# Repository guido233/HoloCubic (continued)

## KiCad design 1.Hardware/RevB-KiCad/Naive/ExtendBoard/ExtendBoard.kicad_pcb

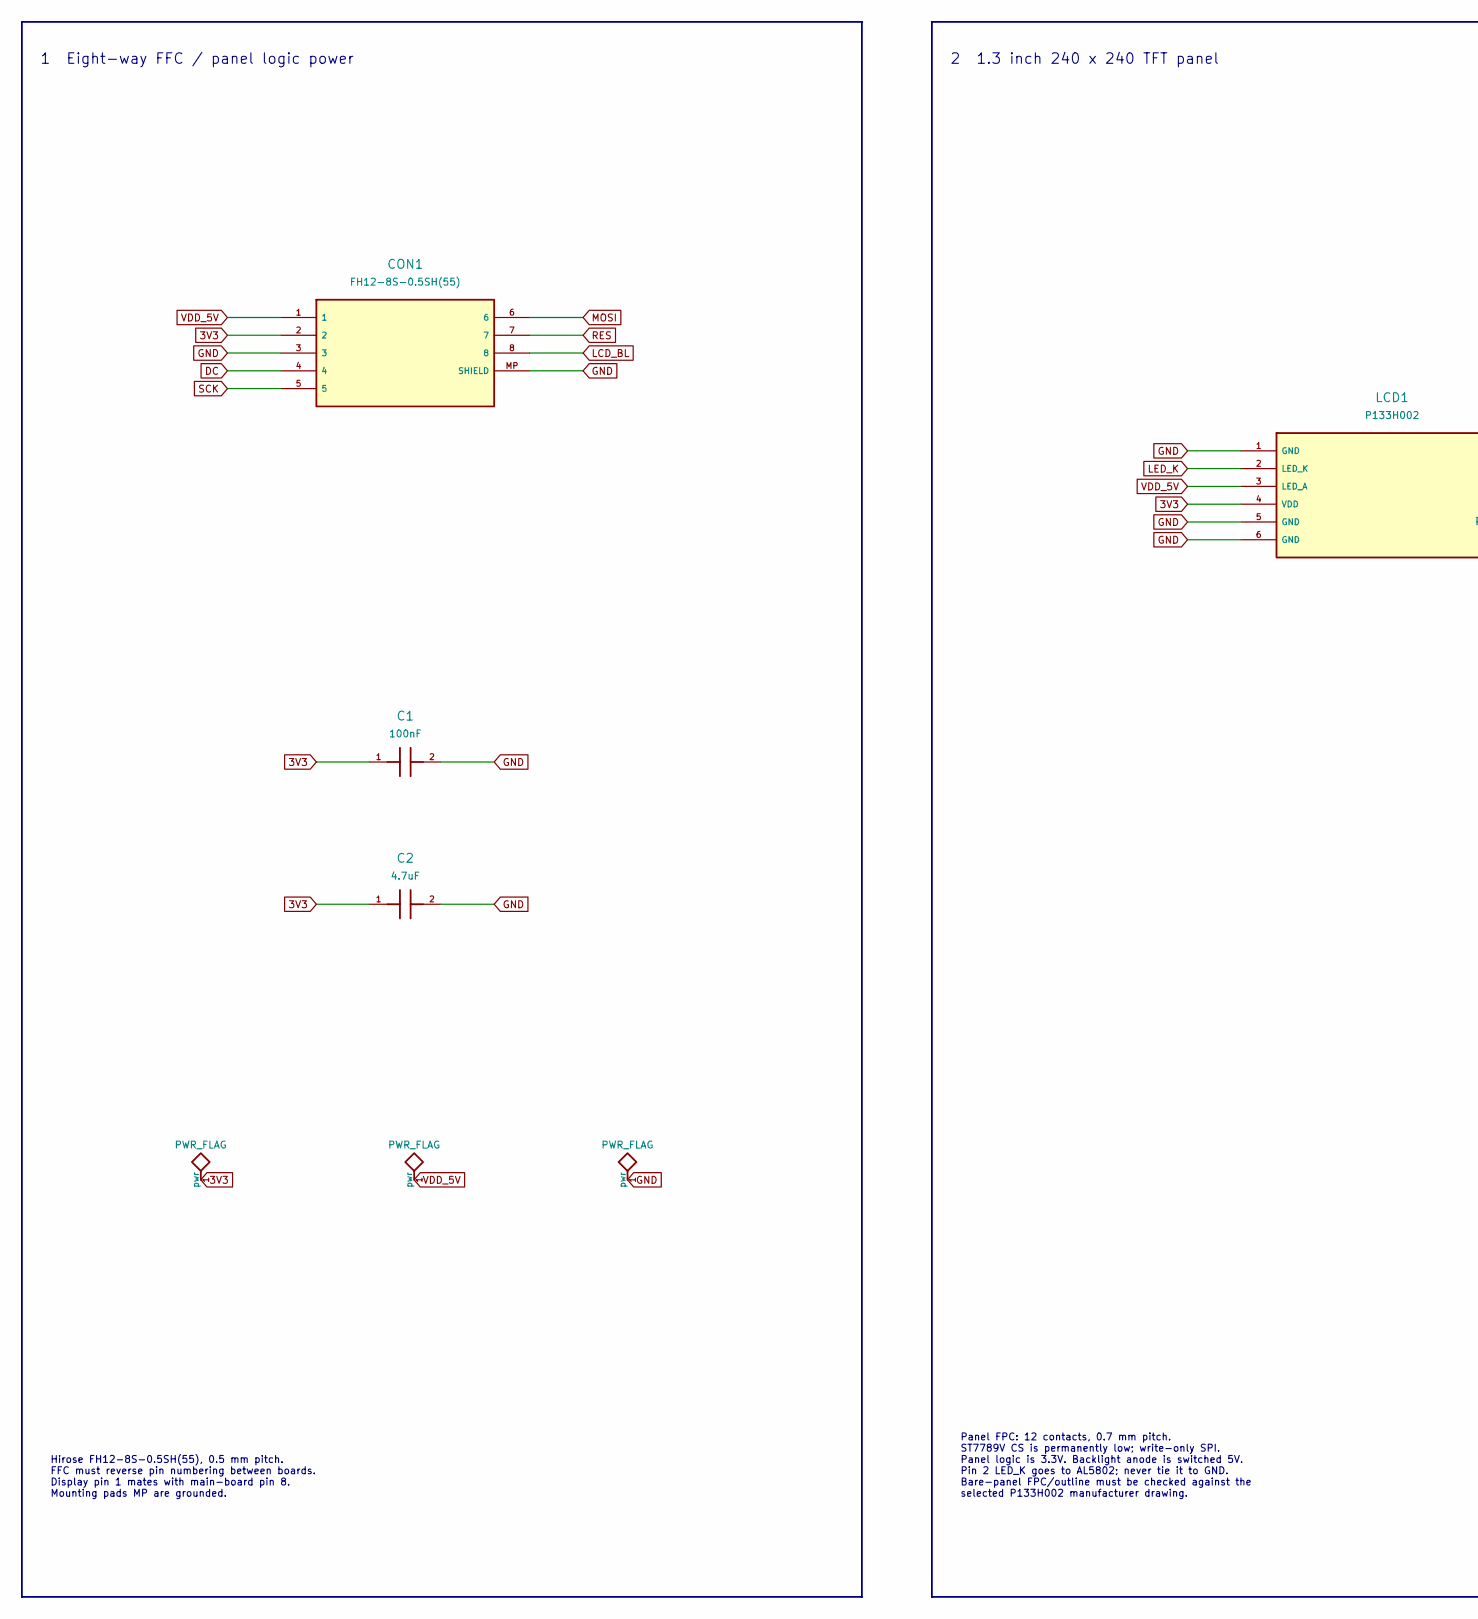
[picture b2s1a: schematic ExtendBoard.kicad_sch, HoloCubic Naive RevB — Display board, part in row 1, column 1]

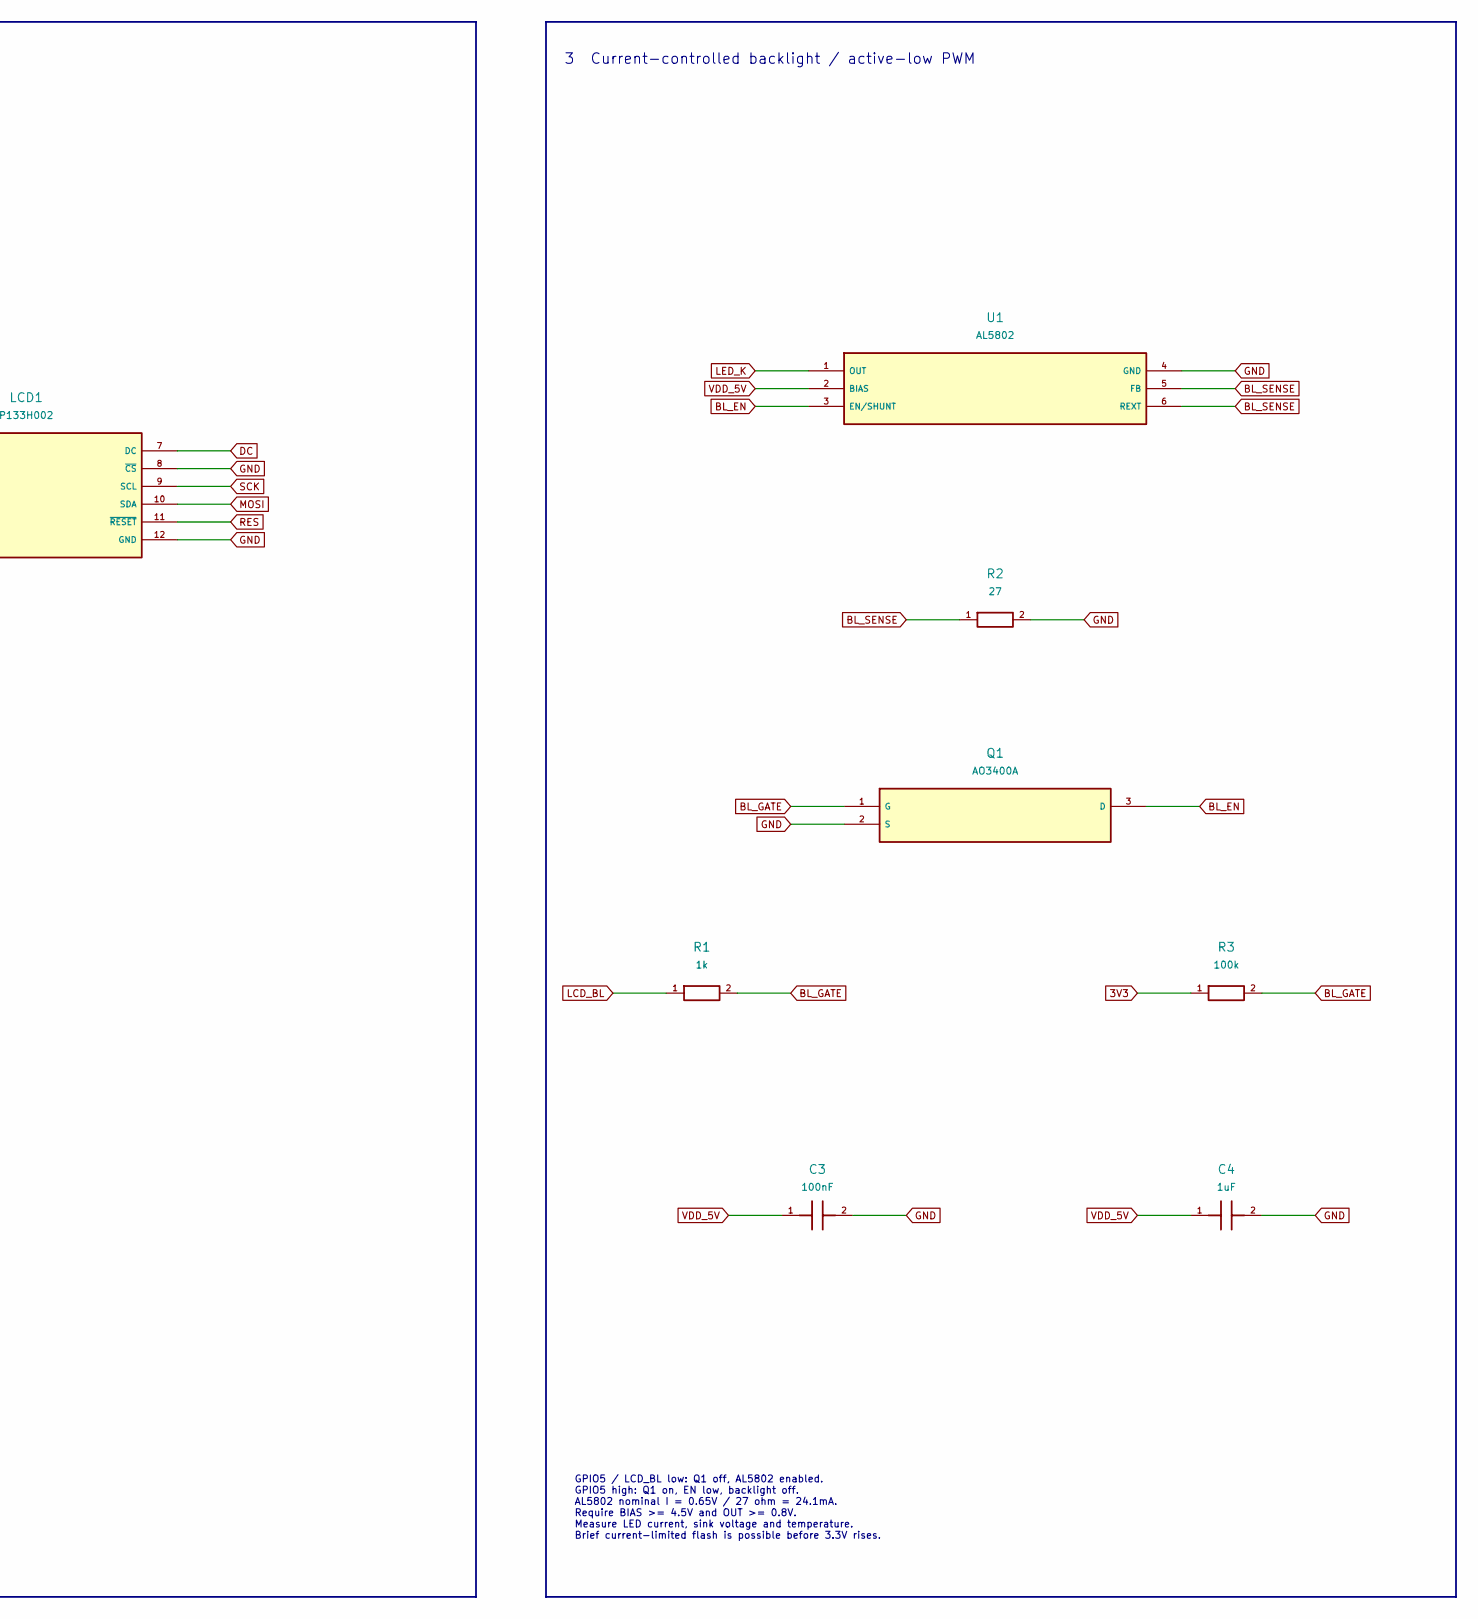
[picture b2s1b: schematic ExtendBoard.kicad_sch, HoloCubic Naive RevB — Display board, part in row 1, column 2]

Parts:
C1, C3: 100nF; C_0402; MPN GRM155R71C104KA88D
C2: 4.7uF; C_0603; MPN GRM188R61A475KE15D
C4: 1uF; C_0603; MPN GRM188R71E105KA12D
CON1: FH12-8S-0.5SH(55); FFC_8P_0.5mm; MPN FH12-8S-0.5SH(55)
LCD1: P133H002; LCD_12P_0.7mm; MPN P133H002
Q1: AO3400A; SOT23_NMOS; MPN AO3400A
R1: 1k; R_0402; MPN RC0402FR-071KL
R2: 27; R_0603; MPN RC0603FR-0727RL
R3: 100k; R_0402; MPN RC0402FR-07100KL
U1: AL5802; SOT26_AL5802; MPN AL5802-7

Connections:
3V3: C1.1, C2.1, CON1.2, LCD1.4 (VDD), R3.1
BL_EN: Q1.3 (D), U1.3 (EN/SHUNT)
BL_GATE: Q1.1 (G), R1.2, R3.2
BL_SENSE: R2.1, U1.5 (FB), U1.6 (REXT)
DC: CON1.4, LCD1.7 (DC)
GND: C1.2, C2.2, C3.2, C4.2, CON1.3, CON1.MP (SHIELD), LCD1.1 (GND), LCD1.5 (GND), LCD1.6 (GND), LCD1.8 (~CS), LCD1.12 (GND), Q1.2 (S), R2.2, U1.4 (GND)
LCD_BL: CON1.8, R1.1
LED_K: LCD1.2 (LED_K), U1.1 (OUT)
MOSI: CON1.6, LCD1.10 (SDA)
RES: CON1.7, LCD1.11 (~RESET)
SCK: CON1.5, LCD1.9 (SCL)
VDD_5V: C3.1, C4.1, CON1.1, LCD1.3 (LED_A), U1.2 (BIAS)

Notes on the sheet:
1 Eight-way FFC / panel logic power
2 1.3 inch 240 x 240 TFT panel
3 Current-controlled backlight / active-low PWM
Hirose FH12-8S-0.5SH(55), 0.5 mm pitch. FFC must reverse pin numbering between boards. Display pin 1 mates with main-board pin 8. Mounting pads MP are grounded.
Panel FPC: 12 contacts, 0.7 mm pitch. ST7789V CS is permanently low; write-only SPI. Panel logic is 3.3V. Backlight anode is switched 5V. Pin 2 LED_K goes to AL5802; never tie it to GND. Bare-panel FPC/outline must be checked against the selected P133H002 manufacturer drawing.
GPIO5 / LCD_BL low: Q1 off, AL5802 enabled. GPIO5 high: Q1 on, EN low, backlight off. AL5802 nominal I = 0.65V / 27 ohm = 24.1mA. Require BIAS >= 4.5V and OUT >= 0.8V. Measure LED current, sink voltage and temperature. Brief current-limited flash is possible before 3.3V rises.

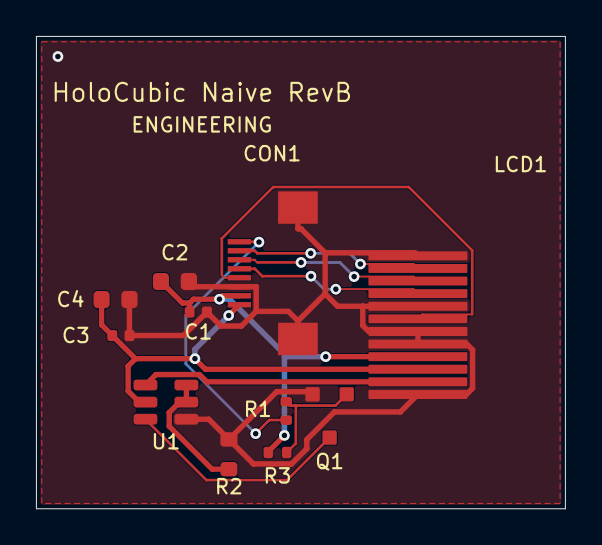
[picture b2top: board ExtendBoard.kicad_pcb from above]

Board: 2 copper layers, 29.4 x 26.2 mm, 11 parts (1 on the bottom side), 12 nets.

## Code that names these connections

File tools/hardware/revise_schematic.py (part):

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        'footprint': 'TF-Card-Amphenol with TF',
        'uuid': '036f4eda-700d-41ff-ba17-68fad1ad7e32',
        'pins': {'1': {'name': 'DATA_LINE[BIT_2]', 'type': 'passive', 'net': None},
                 '2': {'name': 'CARD_DETECT/DATA_LINE[BIT_3]', 'type': 'passive', 'net': 'GPIO15'},
                 '3': {'name': 'COMMAND/RESPONSE', 'type': 'passive', 'net': 'GPIO13'},
                 '4': {'name': 'VCC', 'type': 'passive', 'net': '3V3'},
                 '5': {'name': 'CLOCK', 'type': 'passive', 'net': 'GPIO14'},
                 '6': {'name': 'GND', 'type': 'passive', 'net': 'GND'},
                 '7': {'name': 'DATA_LINE[BIT_0]', 'type': 'passive', 'net': 'GPIO26'},
                 '8': {'name': 'DATA_LINE[BIT_1]', 'type': 'passive', 'net': None},
                 '9': {'name': 'CD_SWITCH1', 'type': 'passive', 'net': 'GND'},
                 '10': {'name': 'CD_SWITCH2', 'type': 'passive', 'net': 'GND'},
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 'R4': {'value': '12K',
        'footprint': 'RES_0402',
        'uuid': '480a12a3-30de-4506-819f-f5caa71d6bf5',
        'pins': {'1': {'name': '1', 'type': 'passive', 'net': 'DTR'},
                 '2': {'name': '2', 'type': 'passive', 'net': 'NetR4_2'}}},
 'USB1': {'value': 'Type-C',
          'footprint': 'Type-C-TOP',
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        'pins': {'1': {'name': 'VDD', 'type': 'power_in', 'net': 'VDD_5V'},
                 '2': {'name': 'DOUT', 'type': 'output', 'net': None},
                 '3': {'name': 'GND', 'type': 'power_in', 'net': 'GND'},
                 '4': {'name': 'DIN', 'type': 'input', 'net': 'GPIO27'}}},
 'R8': {'value': '10K',
        'footprint': 'RES_0402',
        'uuid': '4bc8dee3-f30c-4e77-bfd4-e8b4b71b5e3c',
        'pins': {'1': {'name': '1', 'type': 'passive', 'net': '3V3'},
                 '2': {'name': '2', 'type': 'passive', 'net': 'GPIO13'}}},
 'C2': {'value': '10uF',
        'footprint': 'CAP_0402',
        'uuid': '4edd19f1-0a79-4163-81b8-24c11d2702e3',
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        'footprint': 'RES_0402',
        'uuid': '59df2c9e-d16b-432e-aa8c-63f372a108e6',
        'pins': {'1': {'name': '1', 'type': 'passive', 'net': '3V3'},
                 '2': {'name': '2', 'type': 'passive', 'net': 'GPIO14'}}},
 'R7': {'value': '10K',
        'footprint': 'RES_0402',
        'uuid': '5a997410-384c-4189-9b8c-871480810be4',
        'pins': {'1': {'name': '1', 'type': 'passive', 'net': '3V3'},
                 '2': {'name': '2', 'type': 'passive', 'net': 'GPIO26'}}},
 'U1': {'value': 'CP2102',
        'footprint': 'QFN-28',
        'uuid': '6d990930-ca24-4125-89d4-8b4e6e54561f',
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 'R5': {'value': '12K',
        'footprint': 'RES_0402',
        'uuid': '7286ff2e-9e1b-4bae-ac24-8b4b0fb69403',
        'pins': {'1': {'name': '1', 'type': 'passive', 'net': 'RTS'},
                 '2': {'name': '2', 'type': 'passive', 'net': 'NetR5_2'}}},
 'U2': {'value': 'LP2992 3V3',
        'footprint': 'SOT23-5',
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 'R3': {'value': '200R',
        'footprint': 'RES_0402',
        'uuid': '7b4fecf7-ec40-466a-be5f-b7976867abfa',
        'pins': {'1': {'name': '1', 'type': 'passive', 'net': 'CP_Tx'},
                 '2': {'name': '2', 'type': 'passive', 'net': 'NetR3_2'}}},
 'R2': {'value': '0R',
        'footprint': 'RES_0402',
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         'uuid': '83ae2094-2acd-4f46-aec4-3455790201f2',
         'pins': {'1': {'name': 'B', 'type': 'input', 'net': 'NetR5_2'},
                  '2': {'name': 'E', 'type': 'passive', 'net': 'DTR'},
                  '3': {'name': 'C', 'type': 'open_collector', 'net': 'GPIO0'}}},
 'R6': {'value': '10K',
        'footprint': 'RES_0402',
        'uuid': '89beacb9-08aa-4d86-9ed8-5e2130c5a1e4',
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         'footprint': 'RES_0402',
         'uuid': '9a86d532-7819-4493-8d96-e85e307444ba',
         'pins': {'1': {'name': '1', 'type': 'passive', 'net': '3V3'},
                  '2': {'name': '2', 'type': 'passive', 'net': 'GPIO15'}}},
 'C10': {'value': '0.1uF',
         'footprint': 'CAP_0402',
         'uuid': '9b7b0381-cbbd-4e1e-85f8-db3f8b7ed2db',
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 'CON1': {'value': 'FFC_0.5_8',
          'footprint': 'FFC_0.5_8',
          'uuid': 'b2720441-1512-49fe-ba01-9b313defc353',
          'pins': {'1': {'name': '1', 'type': 'passive', 'net': 'GPIO5'},
                   '2': {'name': '2', 'type': 'passive', 'net': 'GPIO4'},
                   '3': {'name': '3', 'type': 'passive', 'net': 'GPIO23'},
                   '4': {'name': '4', 'type': 'passive', 'net': 'GPIO18'},
                   '5': {'name': '5', 'type': 'passive', 'net': 'DC'},
                   '6': {'name': '6', 'type': 'passive', 'net': 'GND'},
                   '7': {'name': '7', 'type': 'passive', 'net': '3V3'},
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                 '12': {'name': '32K_XP', 'type': 'bidirectional', 'net': 'BH_SDA'},
                 '13': {'name': '32K_XN', 'type': 'bidirectional', 'net': 'BH_SCL'},
                 '14': {'name': 'GPIO25', 'type': 'bidirectional', 'net': None},
                 '15': {'name': 'GPIO26', 'type': 'bidirectional', 'net': 'GPIO26'},
                 '16': {'name': 'GPIO27', 'type': 'bidirectional', 'net': 'GPIO27'},
                 '17': {'name': 'MTMS', 'type': 'bidirectional', 'net': 'GPIO14'},
                 '18': {'name': 'MTDI', 'type': 'bidirectional', 'net': None},
                 '19': {'name': 'VDD3P3_RTC', 'type': 'power_in', 'net': '3V3A'},
                 '20': {'name': 'MTCK', 'type': 'bidirectional', 'net': 'GPIO13'},
                 '21': {'name': 'MTDO', 'type': 'bidirectional', 'net': 'GPIO15'},
                 '22': {'name': 'GPIO2', 'type': 'bidirectional', 'net': 'DC'},
                 '23': {'name': 'GPIO0', 'type': 'bidirectional', 'net': 'GPIO0'},
                 '24': {'name': 'GPIO4', 'type': 'bidirectional', 'net': 'GPIO4'},
                 '25': {'name': 'IO16(FLASH_CS)', 'type': 'bidirectional', 'net': None},
                 '26': {'name': 'VDD_SDIO_NC', 'type': 'no_connect', 'net': None},
                 '27': {'name': 'IO17(FLASH_SD0)', 'type': 'bidirectional', 'net': None},
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                 '31': {'name': 'SD_CLK(FLASH_CLK)', 'type': 'bidirectional', 'net': None},
                 '32': {'name': 'SD_DATA_0(FLASH_SD3)', 'type': 'bidirectional', 'net': None},
                 '33': {'name': 'SD_DATA_1(FLASH_SD1)', 'type': 'bidirectional', 'net': None},
                 '34': {'name': 'GPIO5', 'type': 'bidirectional', 'net': 'GPIO5'},
                 '35': {'name': 'GPIO18', 'type': 'bidirectional', 'net': 'GPIO18'},
                 '36': {'name': 'GPIO23', 'type': 'bidirectional', 'net': 'GPIO23'},
                 '37': {'name': 'VDD3P3_CPU', 'type': 'power_in', 'net': '3V3A'},
                 '38': {'name': 'GPIO19', 'type': 'bidirectional', 'net': None},
                 '39': {'name': 'GPIO22', 'type': 'bidirectional', 'net': None},
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        doc += [rect,text_node(title,x1+2.54,y1+6.35,1.5)]
    notes=[('USB_VBUS = connector raw 5V; VDD_5V = switched system 5V.\nCC1 / CC2 each have an independent 5.1k Rd.',14,155),
           ('ON RC: 100k / 100nF; CT: 100pF C0G. 5V tR approx 0.425ms.\nMeasure CP_VDD rise to 2.7V <=1ms and USB hot-plug current.',214,164),
           ('OE permanently enabled; GPIO27 pulled low at reset.\nD1: Worldsemi WS2812B-V5/W. Series 33 ohm near buffer.',419,152),
           ('CP2102 internal 3.3V is CP_VDD, with C18 local bypass.\nR6 / C7 provide the ESP32 EN reset delay.\nDual NPN DTR/RTS topology retained from the original design.',14,369),
           ('Unused exposed flash / strapping / ADC pins are explicitly NC.\nGPIO32 = SDA; GPIO33 = SCL; GPIO27 = RGB.\nGPIO13/14/15/26 = SD CMD/CLK/CS/DAT0.\nGPIO18/23/2/4/5 = TFT SCK/MOSI/DC/RESET/BL.\nMPU6050: no exposed-pad pin; keep copper/vias/paste out below die.',214,306),
           ('MPU6050 address: 0x68 (AD0=GND); INT not used.\nBH1750 address: 0x23 (ADDR=GND). 4.7k I2C pull-ups.',419,306),
           ('FFC pin order retained. Mate reverses pin numbering.\nGPIO5 low enables the display NMOS / AL5802 backlight stage.\nPins 7=3V3, 8=switched VDD_5V.',419,370)]
    for t,x,y in notes:doc.append(text_node(t,x,y,1.0))
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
